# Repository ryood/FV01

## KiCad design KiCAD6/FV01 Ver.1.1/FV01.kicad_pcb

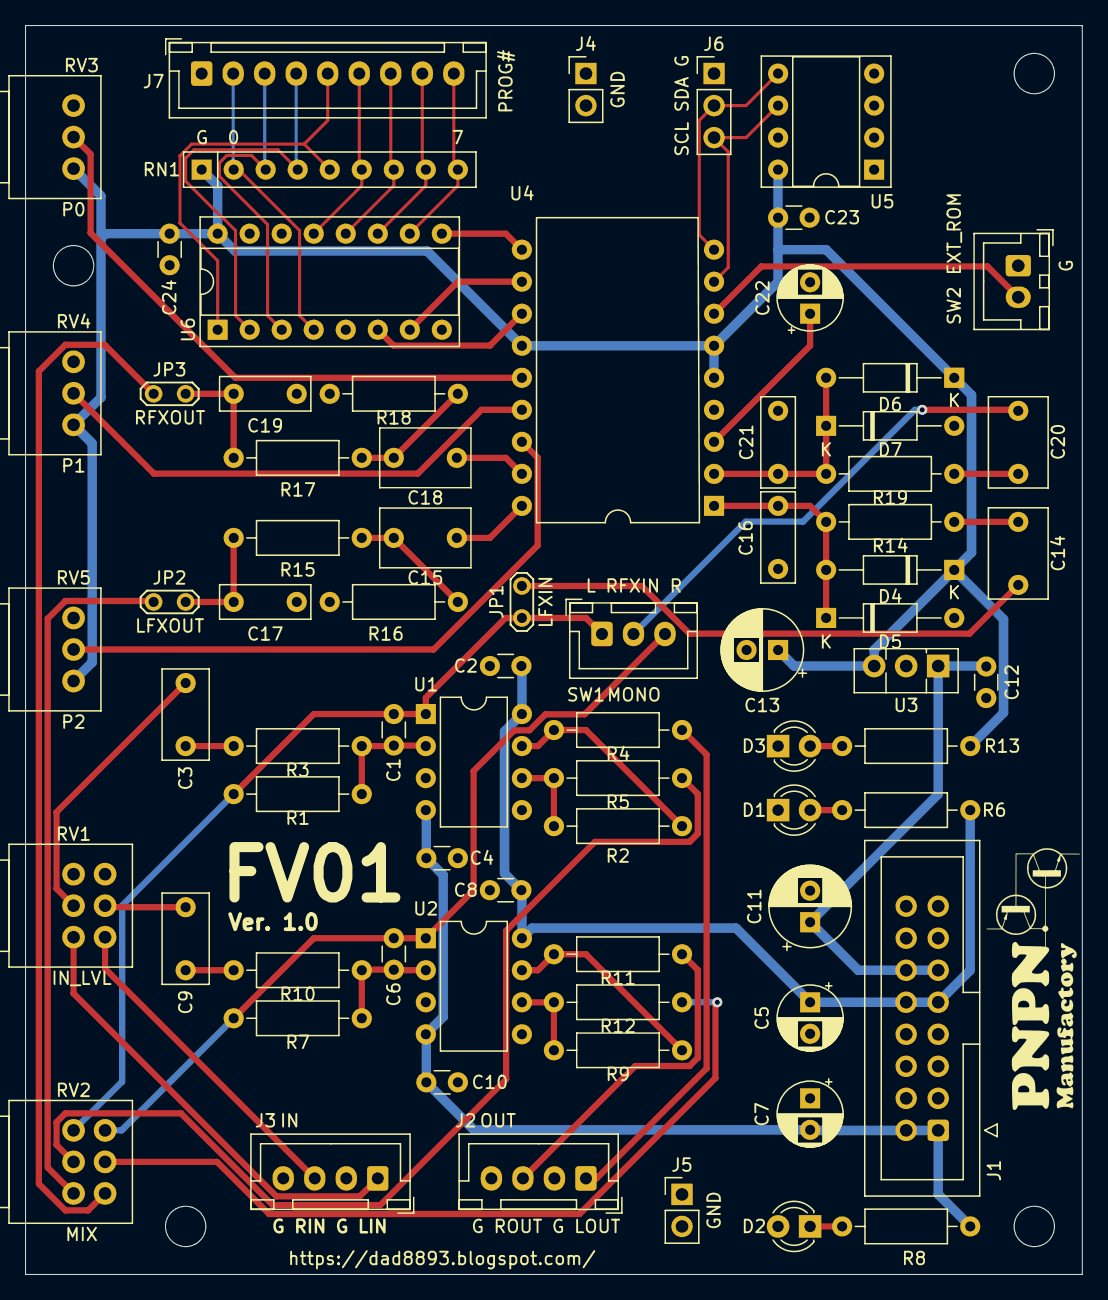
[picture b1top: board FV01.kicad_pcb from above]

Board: 2 copper layers, 83.8 x 99.1 mm, 78 parts (0 on the bottom side), 58 nets.

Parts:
C1, C6: 10p; C_Disc_D3.0mm_W1.6mm_P2.50mm
C2, C4, C8, C10, C12, C23, C24: 0.1u; C_Disc_D3.0mm_W1.6mm_P2.50mm
C3, C9: 0.1u; C_Rect_L7.0mm_W3.5mm_P5.00mm
C5, C7: 47u; CP_Radial_D5.0mm_P2.50mm
C11, C13: 100u; CP_Radial_D6.3mm_P2.50mm
C14, C15, C18, C20: 1u; C_Rect_L7.0mm_W4.5mm_P5.00mm
C16, C21: 1000p(C&T); C_Rect_L7.0mm_W2.5mm_P5.00mm
C17, C19: 2200p(C&T); C_Rect_L7.0mm_W2.5mm_P5.00mm
C22: 1u; CP_Radial_D5.0mm_P2.50mm
D1, D2, D3: LED; LED_D3.0mm
D4, D5, D6, D7: 1SS106; D_DO-35_SOD27_P10.16mm_Horizontal
H1, H2, H3, H4: MountingHole; MountingHole_3.2mm_M3
J1: ERK_PWR; IDC-Header_2x08_P2.54mm_Vertical
J2: OUT; JST_XH_B4B-XH-A_1x04_P2.50mm_Vertical
J3: IN; JST_XH_B4B-XH-A_1x04_P2.50mm_Vertical
J4, J5: TP_GND; PinHeader_1x02_P2.54mm_Vertical
J6: PROG; PinHeader_1x03_P2.54mm_Vertical
J7: SW_PROG; JST_XH_B9B-XH-A_1x09_P2.50mm_Vertical
JP1, JP2, JP3: Jumper; TestPoint_2Pads_Pitch2.54mm_Drill0.8mm
R1, R7: 100k; R_Axial_DIN0207_L6.3mm_D2.5mm_P10.16mm_Horizontal
R2, R9: 330k(C&T); R_Axial_DIN0207_L6.3mm_D2.5mm_P10.16mm_Horizontal
R3, R10: 330k; R_Axial_DIN0207_L6.3mm_D2.5mm_P10.16mm_Horizontal
R4, R11, R13, R14, R15, R17, R19: 1k; R_Axial_DIN0207_L6.3mm_D2.5mm_P10.16mm_Horizontal
R5, R12: 100k(C&T); R_Axial_DIN0207_L6.3mm_D2.5mm_P10.16mm_Horizontal
R6, R8: 4.7k; R_Axial_DIN0207_L6.3mm_D2.5mm_P10.16mm_Horizontal
R16, R18: 33k(C&T); R_Axial_DIN0207_L6.3mm_D2.5mm_P10.16mm_Horizontal
RN1: 4.7k x8; R_Array_SIP9
RV1: 50k/A; Potentiometer_Alps_RK097_Dual_Horizontal
RV2: 50k/B; Potentiometer_Alps_RK097_Dual_Horizontal
RV3, RV4, RV5: 50k/B; Potentiometer_Alps_RK097_Single_Horizontal
SW1: SW_MONO; JST_XH_B3B-XH-A_1x03_P2.50mm_Vertical
SW2: SW_EEPROM; JST_XH_B2B-XH-A_1x02_P2.50mm_Vertical
U1, U2: TL072; DIP-8_W7.62mm
U3: TA48M033F; TO-126-3_Vertical
U4: AE-FV-1-DIP_large; DIP-18_W15.24mm
U5: 24LC32; DIP-8_W7.62mm_Socket
U6: 74HC148; DIP-16_W7.62mm_Socket

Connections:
+3V3: C13.1, C23.1, C24.1, D4.1, D6.1, R13.1, RN1.1, RV3.3, RV4.3, RV5.3, U3.3, U4.5, U4.6, U4.13, U5.8, U6.16
+5V: C11.1, C12.1, J1.11, J1.12, U3.1
+12V: C2.2, C5.1, C8.2, J1.9, J1.10, R6.1, U1.8, U2.8
-12V: C4.2, C7.2, C10.2, J1.1, J1.2, R8.2, U1.4, U2.4
/FV-1/LFXIN: C14.2, JP1.2
/FV-1/LFXOUT: C17.1, JP2.1, R15.1
/FV-1/RFXIN: C20.2, SW1.2
/FV-1/RFXOUT: C19.1, JP3.1, R17.1
/FV-1/SCL: J6.3, U4.8, U5.6
/FV-1/SDA: J6.2, U4.9, U5.5
/LIN: J3.1, RV1.3
/LOUT: J2.1, R4.1
/RIN: J3.3, RV1.6
/ROUT: J2.3, R11.1
GND: C2.1, C4.1, C5.2, C7.1, C8.1, C10.1, C11.2, C12.2, C13.2, C16.2, C17.2, C19.2, C21.2, C22.2, C23.2, C24.2, D1.1, D2.2, D3.1, D5.2, D7.2, J1.3, J1.4, J1.5, J1.6, J1.7, J1.8, J2.2, J2.4, J3.2, J3.4, J4.1, J4.2, J5.1, J5.2, J6.1, J7.1, R16.1, R18.1, RV1.1, RV1.4, RV3.1, RV4.1, RV5.1, SW2.1, U1.3, U1.5, U2.3, U2.5, U3.2, U4.4, U5.1, U5.2, U5.3, U5.4, U5.7, U6.5, U6.8
unnamed: C1.1, JP1.1, R1.1, RV2.1, SW1.1, U1.1
unnamed: C1.2, R1.2, R3.1, U1.2
unnamed: C3.1, R3.2
unnamed: C3.2, RV1.2
unnamed: C6.1, R7.1, RV2.4, SW1.3, U2.1
unnamed: C6.2, R7.2, R10.1, U2.2
unnamed: C9.1, R10.2
unnamed: C9.2, RV1.5
unnamed: C14.1, R14.2
unnamed: C15.1, R15.2, R16.2
unnamed: C15.2, U4.18
unnamed: C16.1, D4.2, D5.1, R14.1, U4.1
unnamed: C18.1, R17.2, R18.2
unnamed: C18.2, U4.17
unnamed: C20.1, R19.2
unnamed: C21.1, D6.2, D7.1, R19.1, U4.2
unnamed: C22.1, U4.3
unnamed: D1.2, R6.2
unnamed: D2.1, R8.1
unnamed: D3.2, R13.2
unnamed: J7.2, RN1.2, U6.4
unnamed: J7.3, RN1.3, U6.3
unnamed: J7.4, RN1.4, U6.2
unnamed: J7.5, RN1.5, U6.1
unnamed: J7.6, RN1.6, U6.13
unnamed: J7.7, RN1.7, U6.12
unnamed: J7.8, RN1.8, U6.11
unnamed: J7.9, RN1.9, U6.10
unnamed: JP2.2, RV2.3
unnamed: JP3.2, RV2.6
unnamed: R2.1, R4.2, U1.7
unnamed: R2.2, R5.1, U1.6
unnamed: R5.2, RV2.2
unnamed: R9.1, R11.2, U2.7
unnamed: R9.2, R12.1, U2.6
unnamed: R12.2, RV2.5
unnamed: RV3.2, U4.14
unnamed: RV4.2, U4.15
unnamed: RV5.2, U4.16
unnamed: SW2.2, U4.7
unnamed: U4.10, U6.9
unnamed: U4.11, U6.7
unnamed: U4.12, U6.6

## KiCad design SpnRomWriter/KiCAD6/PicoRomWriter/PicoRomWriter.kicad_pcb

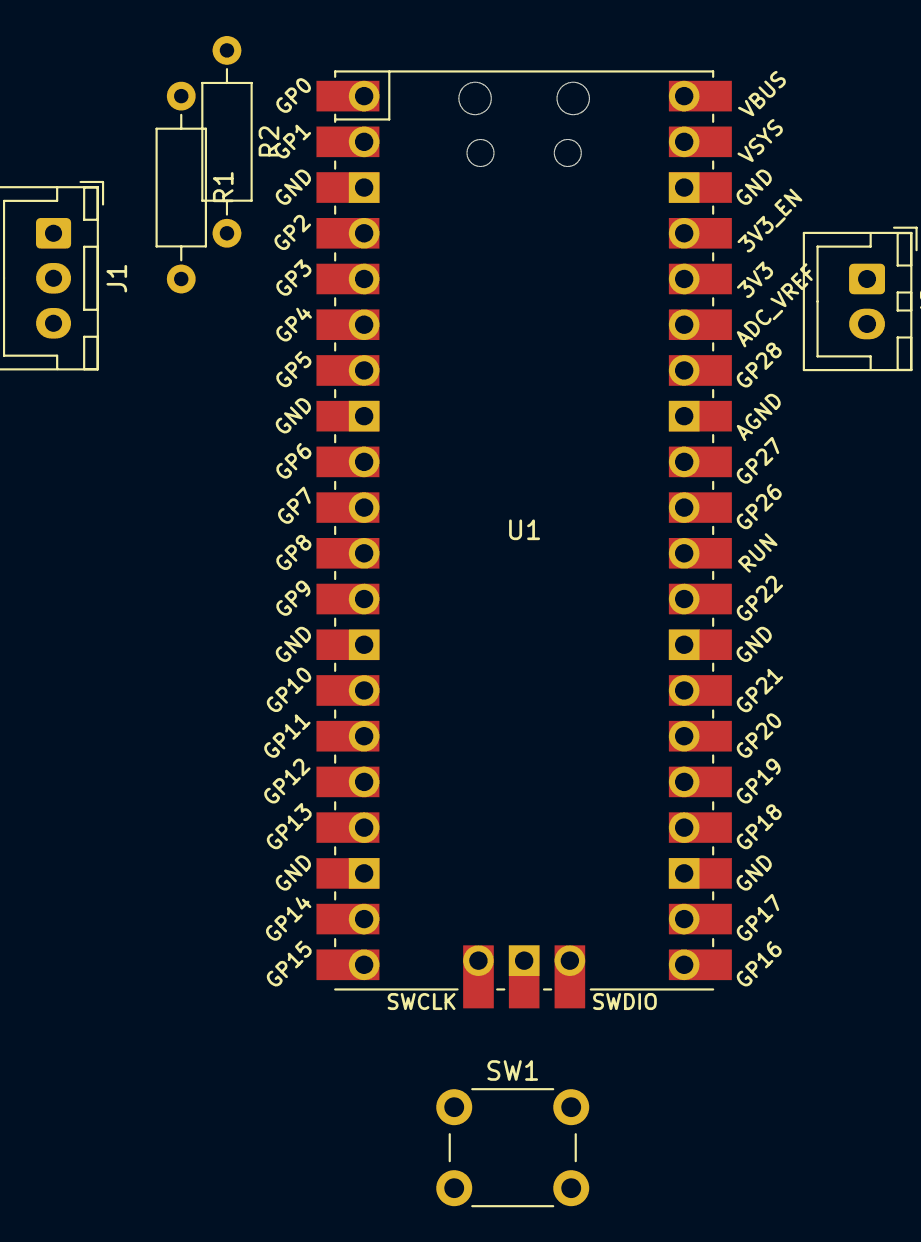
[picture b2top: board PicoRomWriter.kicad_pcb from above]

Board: 2 copper layers, 6 parts (0 on the bottom side), 5 nets, no tracks yet.

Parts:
J1: I2C; JST_XH_B3B-XH-A_1x03_P2.50mm_Vertical
J2: PWR_OUT; JST_XH_B2B-XH-A_1x02_P2.50mm_Vertical
R1, R2: 4.7k; R_Axial_DIN0207_L6.3mm_D2.5mm_P10.16mm_Horizontal
SW1: RESET; SW_PUSH_6mm_H8.5mm
U1: Pico; RPi_Pico_SMD_TH

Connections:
+3V3: J2.1, R1.1, R2.1, U1.36 (3V3)
/SCL: J1.2, R1.2, U1.5 (GPIO3)
/SDA: J1.1, R2.2, U1.4 (GPIO2)
GND: J1.3, J2.2, SW1.2, U1.8 (GND)
unnamed: SW1.1, U1.30 (RUN)

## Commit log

2022-08-11 Panel design
2022-08-20 Blog update
2022-08-25 Blog update No.3 SpinRomWriter
2022-08-28 Blog update No.4 改善策
2022-10-08 Ver.1.1 begin
